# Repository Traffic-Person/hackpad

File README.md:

# hackpad
this is a hackpad that i made to be more productive and to serve as a media player :)

I made this to learn about "professional" hardware and prototype making 

# [Bill Of Materials](/bom.csv)

# Schematics 

It took me like 3 tries

# Pcb

Aint the prettiest but it took me like 4 tries

# 3d Model

Same with the pcb isnt the prettiest but it took me in total ~15 hours (Everything took ~15 hours)

# Final Render 

please forgive the rotary encoder being pink and orange i could not for the life of me find the step file for it

# Early Prototypes

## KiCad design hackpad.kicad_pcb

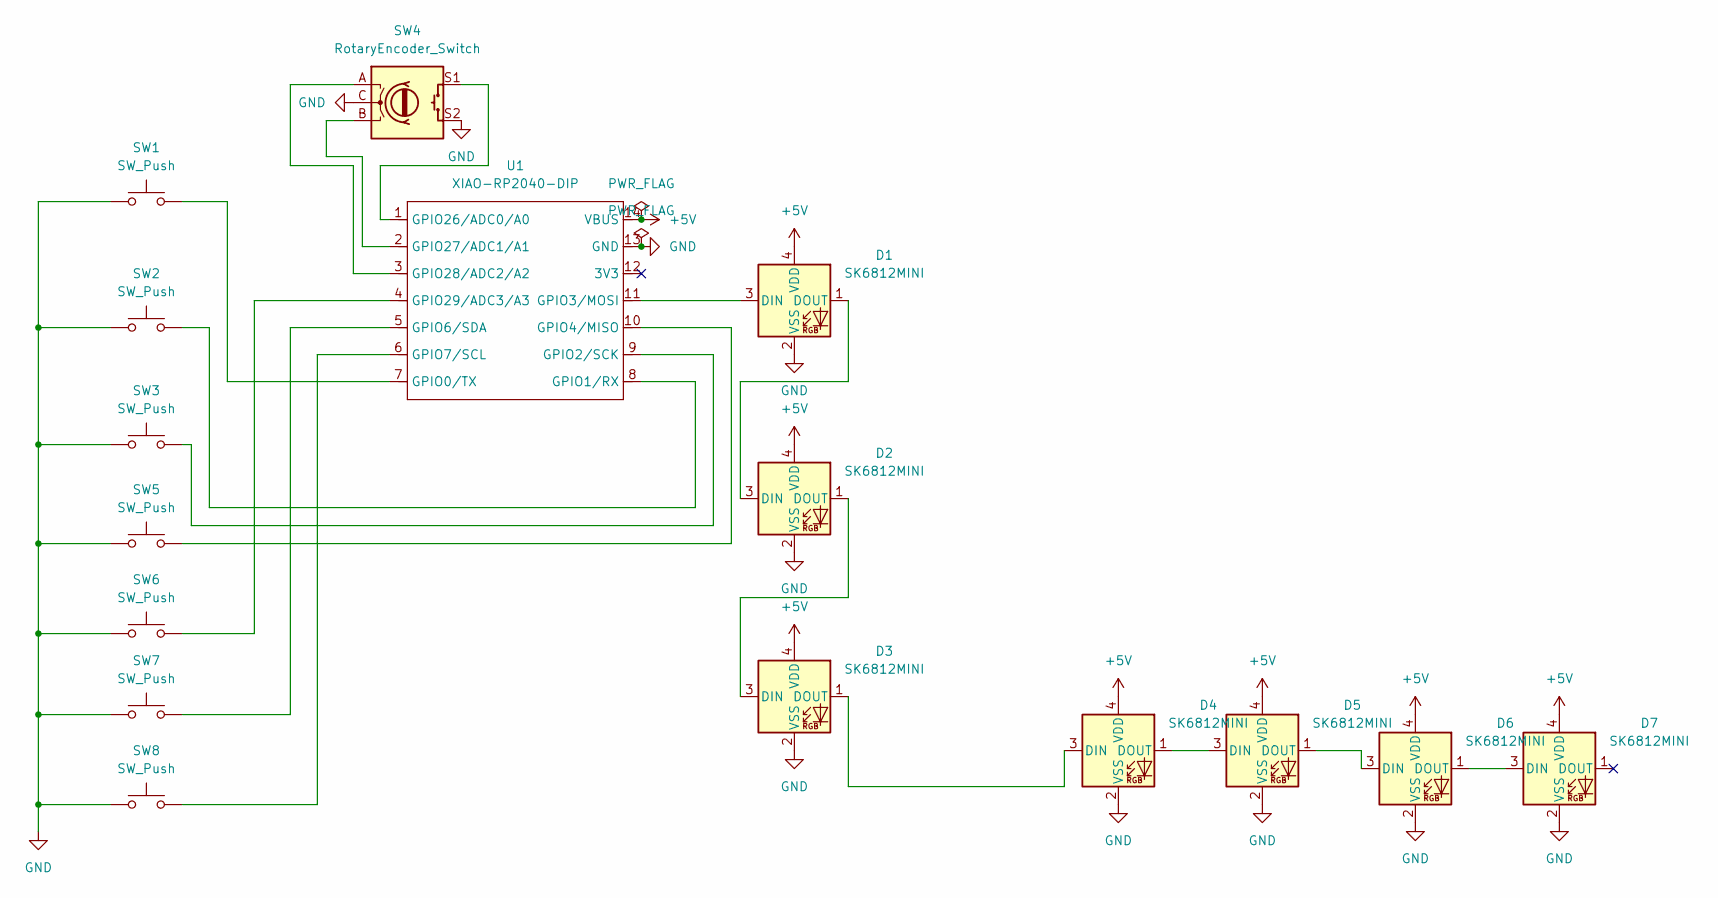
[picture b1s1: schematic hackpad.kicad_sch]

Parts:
D1, D2, D3, D4, D5, D6, D7: SK6812MINI; LED_SK6812MINI_PLCC4_3.5x3.5mm_P1.75mm
SW1, SW2, SW3, SW5, SW6, SW7, SW8: SW_Push; SW_Cherry_MX_1.00u_PCB
SW4: RotaryEncoder_Switch; RotaryEncoder_Alps_EC11E-Switch_Vertical_H20mm
U1: XIAO-RP2040-DIP

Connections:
+5V: D1.4 (VDD), D2.4 (VDD), D3.4 (VDD), D4.4 (VDD), D5.4 (VDD), D6.4 (VDD), D7.4 (VDD), U1.14 (VBUS)
GND: D1.2 (VSS), D2.2 (VSS), D3.2 (VSS), D4.2 (VSS), D5.2 (VSS), D6.2 (VSS), D7.2 (VSS), SW1.1, SW2.1, SW3.1, SW4.C, SW4.S2, SW5.1, SW6.1, SW7.1, SW8.1, U1.13 (GND)
unnamed: D1.3 (DIN), U1.11 (GPIO3/MOSI)
unnamed: D1.1 (DOUT), D2.3 (DIN)
unnamed: D2.1 (DOUT), D3.3 (DIN)
unnamed: D3.1 (DOUT), D4.3 (DIN)
unnamed: D4.1 (DOUT), D5.3 (DIN)
unnamed: D5.1 (DOUT), D6.3 (DIN)
unnamed: D6.1 (DOUT), D7.3 (DIN)
unnamed: SW1.2, U1.7 (GPIO0/TX)
unnamed: SW2.2, U1.8 (GPIO1/RX)
unnamed: SW3.2, U1.9 (GPIO2/SCK)
unnamed: SW5.2, U1.10 (GPIO4/MISO)
unnamed: SW7.2, U1.5 (GPIO6/SDA)
unnamed: SW8.2, U1.6 (GPIO7/SCL)
unnamed: SW4.S1, U1.1 (GPIO26/ADC0/A0)
unnamed: SW4.B, U1.2 (GPIO27/ADC1/A1)
unnamed: SW4.A, U1.3 (GPIO28/ADC2/A2)
unnamed: SW6.2, U1.4 (GPIO29/ADC3/A3)

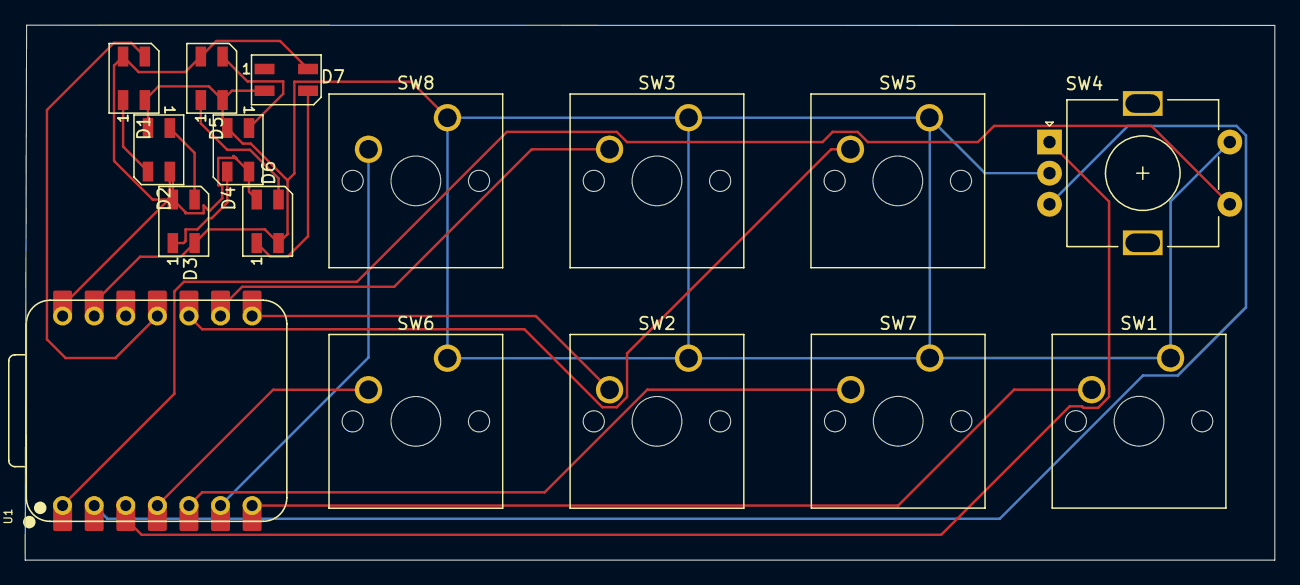
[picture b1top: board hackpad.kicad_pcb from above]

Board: 2 copper layers, 100.5 x 43.0 mm, 16 parts (0 on the bottom side), 19 nets.

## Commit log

2025-11-30 readme
    Added detailed project description, bill of materials, and images.
2025-11-30 Update README with effort description for schematics
    Clarify the effort taken to create the schematics.
2025-11-30 Add early prototype images to README
    Added early prototype images to the README.
2025-11-30 Add MIT License to the project
2025-11-30 Add link to shared Google Drive folder
2025-11-30 Integrate rotary encoder and neopixel control
    Refactored the keyboard handling code to include rotary encoder and neopixel functionality.
2025-11-30 Update 3D print availability note in README
    Clarified the status of 3D printing availability at school.
2025-11-30 Revise PCB pricing and total cost in README
    Updated prices for PCB and total cost in the README.
2025-12-02 Add link to firmware library in new file
2025-12-02 Add main.py for controlling HID devices and LEDs
2025-12-02 Add note about forgotten files
    Add note about forgotten files to file.txt
2025-12-02 Add final render section with images
    Added final render images to the README.
2025-12-02 Document rotary encoder color issue in README
    Added a note about the rotary encoder color issue.
2025-12-02 Add BOM with PCB cost details
2025-12-02 Update bom.csv with links and cost adjustments
    Added links for components and updated costs.
2025-12-02 Revise component entries in bom.csv
    Updated item details for components in the bill of materials.
2025-12-02 Refactor bom.csv for cost and link updates
    Updated cost format and links in bom.csv.
2025-12-02 Remove bill of materials from README
    Removed the bill of materials section from the README.
